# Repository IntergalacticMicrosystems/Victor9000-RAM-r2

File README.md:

# Victor9000-RAM-r2

WORK IN PROGRESS ~ DO NOT USE YET

The Victor9000-RAM-r2 is an attempt to modernize the design for cheaper manufacturing.

Jumper JP1 open is for use on a 256k motherboard, and JP1 closed is for a 128k motherboard.

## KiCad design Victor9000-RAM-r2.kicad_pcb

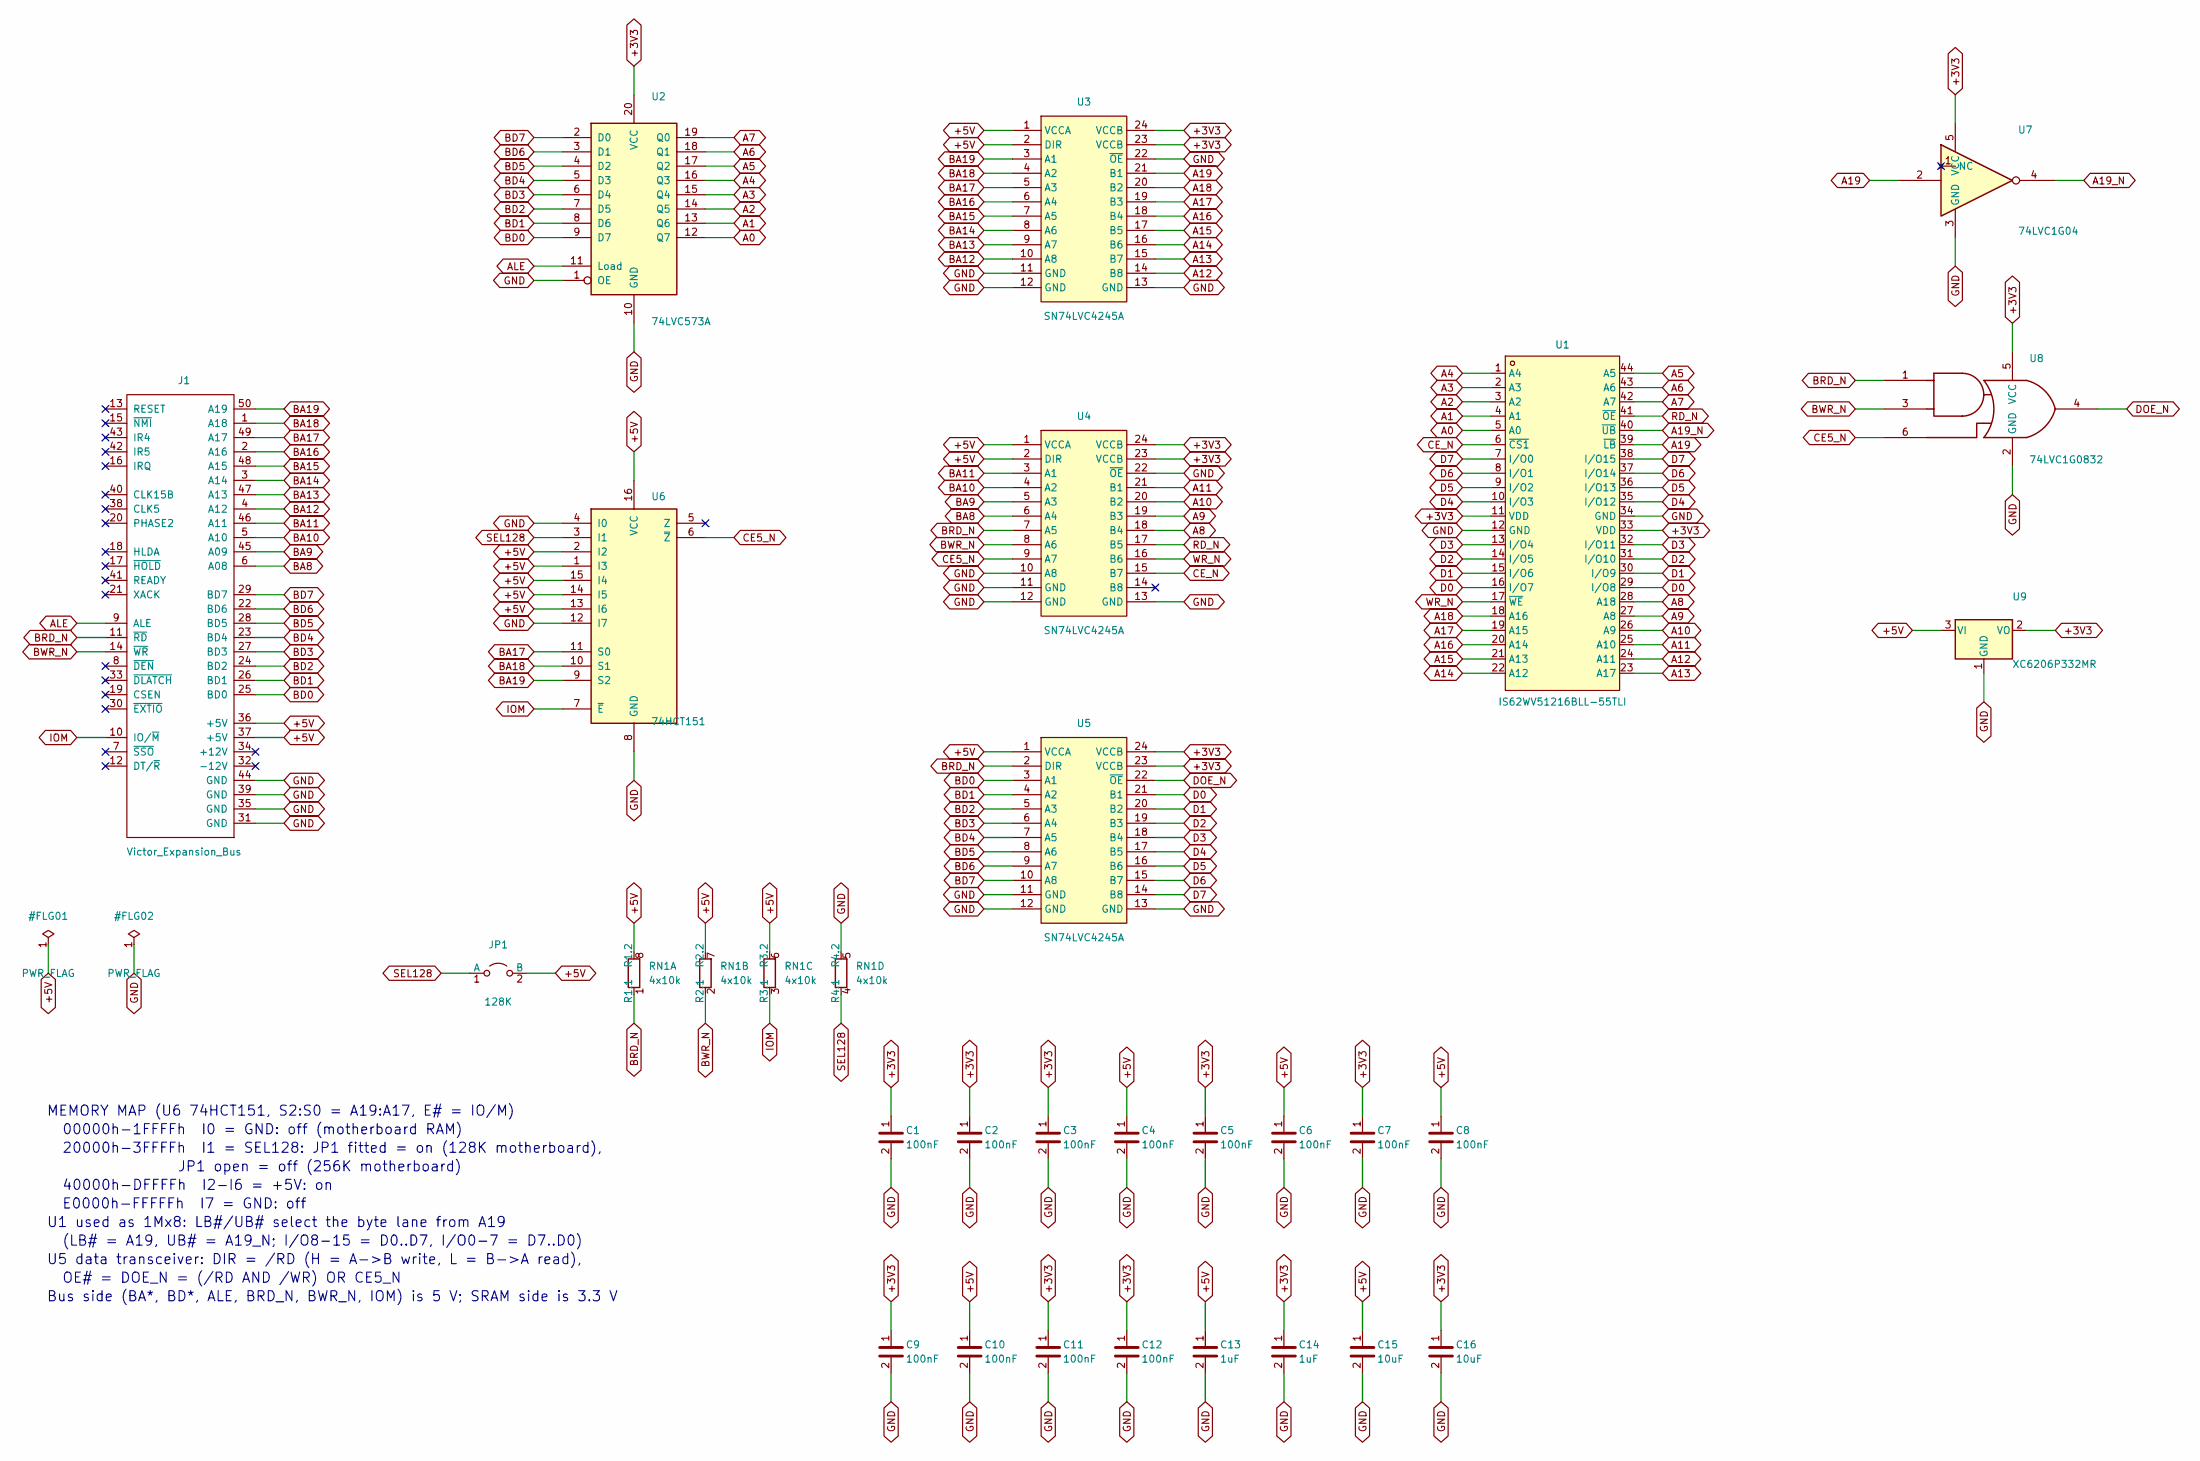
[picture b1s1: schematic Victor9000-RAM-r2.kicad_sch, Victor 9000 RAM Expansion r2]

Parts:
C1, C2, C3, C4, C5, C6, C7, C8, C9, C10, C11, C12: 100nF; C_0603_1608Metric; MPN CC0603KRX7R9BB104; LCSC C14663
C13, C14: 1uF; C_0603_1608Metric; MPN CL10A105KB8NNNC; LCSC C15849
C15, C16: 10uF; C_0805_2012Metric; MPN CL21A106KAYNNNE; LCSC C15850
J1: Victor_Expansion_Bus; Victor Expansion Edge Connector; MPN card-edge fingers
JP1: 128K; PinHeader_1x02_P2.54mm_Horizontal; MPN PZ254R-11-02P; LCSC C492410
RN1: 4x10k; R_Array_Convex_4x0603; MPN 4D03WGJ0103T5E; LCSC C29718
U1: IS62WV51216BLL-55TLI; TSOP-II-44_10.16x18.41mm_P0.8mm; MPN IS62WV51216BLL-55TLI; LCSC C11315
U2: 74LVC573A; TSSOP-20_4.4x6.5mm_P0.65mm; MPN 74LVC573APW,118; LCSC C6096
U3, U4, U5: SN74LVC4245A; TSSOP-24_4.4x7.8mm_P0.65mm; MPN SN74LVC4245APWR; LCSC C7859
U6: 74HCT151; SOIC-16_3.9x9.9mm_P1.27mm; MPN 74HCT151D,653; LCSC C547364
U7: 74LVC1G04; SOT-23-5; MPN SN74LVC1G04DBVR; LCSC C19829658
U8: 74LVC1G0832; SOT-23-6; MPN SN74LVC1G0832DBVR; LCSC C206101
U9: XC6206P332MR; SOT-23; MPN XC6206P332MR-G; LCSC C5446

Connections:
+3V3: C1.1, C2.1, C3.1, C5.1, C7.1, C9.1, C11.1, C12.1, C14.1, C16.1, U1.11 (VDD), U1.33 (VDD), U2.20 (VCC), U3.23 (VCCB), U3.24 (VCCB), U4.23 (VCCB), U4.24 (VCCB), U5.23 (VCCB), U5.24 (VCCB), U7.5 (VCC), U8.5 (VCC), U9.2 (VO)
+5V: C4.1, C6.1, C8.1, C10.1, C13.1, C15.1, J1.36 (+5V), J1.37 (+5V), JP1.2 (B), RN1.6 (R3.2), RN1.7 (R2.2), RN1.8 (R1.2), U3.1 (VCCA), U3.2 (DIR), U4.1 (VCCA), U4.2 (DIR), U5.1 (VCCA), U6.1 (I3), U6.2 (I2), U6.13 (I6), U6.14 (I5), U6.15 (I4), U6.16 (VCC), U9.3 (VI)
A0: U1.5 (A0), U2.12 (Q7)
A1: U1.4 (A1), U2.13 (Q6)
A2: U1.3 (A2), U2.14 (Q5)
A3: U1.2 (A3), U2.15 (Q4)
A4: U1.1 (A4), U2.16 (Q3)
A5: U1.44 (A5), U2.17 (Q2)
A6: U1.43 (A6), U2.18 (Q1)
A7: U1.42 (A7), U2.19 (Q0)
A8: U1.28 (A18), U4.18 (B4)
A9: U1.27 (A8), U4.19 (B3)
A10: U1.26 (A9), U4.20 (B2)
A11: U1.25 (A10), U4.21 (B1)
A12: U1.24 (A11), U3.14 (B8)
A13: U1.23 (A17), U3.15 (B7)
A14: U1.22 (A12), U3.16 (B6)
A15: U1.21 (A13), U3.17 (B5)
A16: U1.20 (A14), U3.18 (B4)
A17: U1.19 (A15), U3.19 (B3)
A18: U1.18 (A16), U3.20 (B2)
A19: U1.39 (~LB), U3.21 (B1), U7.2
A19_N: U1.40 (~UB), U7.4
ALE: J1.9 (ALE), U2.11 (Load)
BA8: J1.6 (A08), U4.6 (A4)
BA9: J1.45 (A09), U4.5 (A3)
BA10: J1.5 (A10), U4.4 (A2)
BA11: J1.46 (A11), U4.3 (A1)
BA12: J1.4 (A12), U3.10 (A8)
BA13: J1.47 (A13), U3.9 (A7)
BA14: J1.3 (A14), U3.8 (A6)
BA15: J1.48 (A15), U3.7 (A5)
BA16: J1.2 (A16), U3.6 (A4)
BA17: J1.49 (A17), U3.5 (A3), U6.11 (S0)
BA18: J1.1 (A18), U3.4 (A2), U6.10 (S1)
BA19: J1.50 (A19), U3.3 (A1), U6.9 (S2)
BD0: J1.25 (BD0), U2.9 (D7), U5.3 (A1)
BD1: J1.26 (BD1), U2.8 (D6), U5.4 (A2)
BD2: J1.24 (BD2), U2.7 (D5), U5.5 (A3)
BD3: J1.27 (BD3), U2.6 (D4), U5.6 (A4)
BD4: J1.23 (BD4), U2.5 (D3), U5.7 (A5)
BD5: J1.28 (BD5), U2.4 (D2), U5.8 (A6)
BD6: J1.22 (BD6), U2.3 (D1), U5.9 (A7)
BD7: J1.29 (BD7), U2.2 (D0), U5.10 (A8)
BRD_N: J1.11 (~RD), RN1.1 (R1.1), U4.7 (A5), U5.2 (DIR), U8.1
BWR_N: J1.14 (~WR), RN1.2 (R2.1), U4.8 (A6), U8.3
CE5_N: U4.9 (A7), U6.6 (~Z), U8.6
CE_N: U1.6 (~CS1), U4.15 (B7)
D0: U1.16 (I/O7), U1.29 (I/O8), U5.21 (B1)
D1: U1.15 (I/O6), U1.30 (I/O9), U5.20 (B2)
D2: U1.14 (I/O5), U1.31 (I/O10), U5.19 (B3)
D3: U1.13 (I/O4), U1.32 (I/O11), U5.18 (B4)
D4: U1.10 (I/O3), U1.35 (I/O12), U5.17 (B5)
D5: U1.9 (I/O2), U1.36 (I/O13), U5.16 (B6)
D6: U1.8 (I/O1), U1.37 (I/O14), U5.15 (B7)
D7: U1.7 (I/O0), U1.38 (I/O15), U5.14 (B8)
DOE_N: U5.22 (~OE), U8.4
GND: C1.2, C2.2, C3.2, C4.2, C5.2, C6.2, C7.2, C8.2, C9.2, C10.2, C11.2, C12.2, C13.2, C14.2, C15.2, C16.2, J1.31 (GND), J1.35 (GND), J1.39 (GND), J1.44 (GND), RN1.5 (R4.2), U1.12 (GND), U1.34 (GND), U2.1 (OE), U2.10 (GND), U3.11 (GND), U3.12 (GND), U3.13 (GND), U3.22 (~OE), U4.10 (A8), U4.11 (GND), U4.12 (GND), U4.13 (GND), U4.22 (~OE), U5.11 (GND), U5.12 (GND), U5.13 (GND), U6.4 (I0), U6.8 (GND), U6.12 (I7), U7.3 (GND), U8.2 (GND), U9.1 (GND)
IOM: J1.10 (IO/~M), RN1.3 (R3.1), U6.7 (~E)
RD_N: U1.41 (~OE), U4.17 (B5)
SEL128: JP1.1 (A), RN1.4 (R4.1), U6.3 (I1)
WR_N: U1.17 (~WE), U4.16 (B6)

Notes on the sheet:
MEMORY MAP (U6 74HCT151, S2:S0 = A19:A17, E# = IO/M)
00000h-1FFFFh I0 = GND: off (motherboard RAM)
20000h-3FFFFh I1 = SEL128: JP1 fitted = on (128K motherboard),
JP1 open = off (256K motherboard)
40000h-DFFFFh I2-I6 = +5V: on
E0000h-FFFFFh I7 = GND: off
U1 used as 1Mx8: LB#/UB# select the byte lane from A19
(LB# = A19, UB# = A19_N; I/O8-15 = D0..D7, I/O0-7 = D7..D0)
U5 data transceiver: DIR = /RD (H = A->B write, L = B->A read),
OE# = DOE_N = (/RD AND /WR) OR CE5_N
Bus side (BA*, BD*, ALE, BRD_N, BWR_N, IOM) is 5 V; SRAM side is 3.3 V

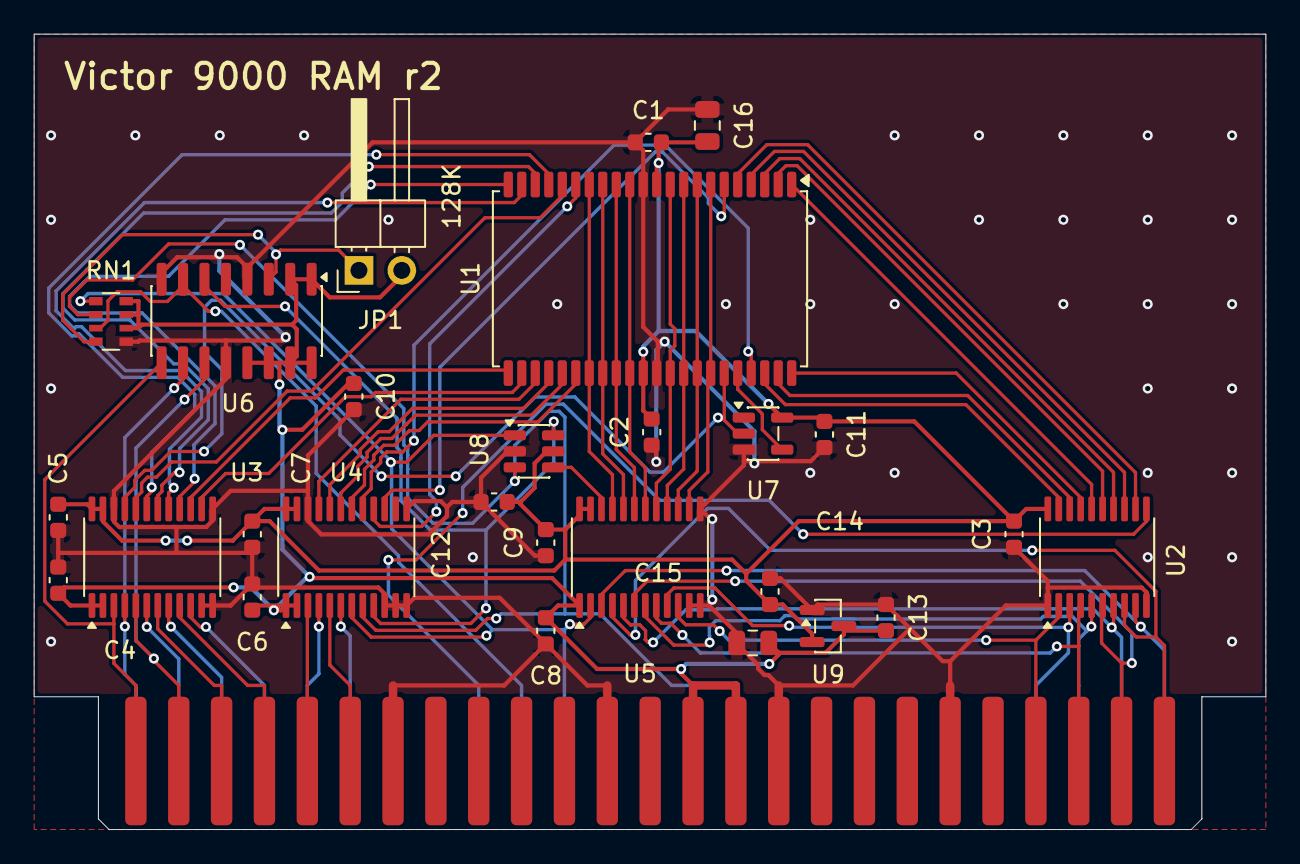
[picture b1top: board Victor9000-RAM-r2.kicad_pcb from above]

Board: 2 copper layers, 73.0 x 47.1 mm, 28 parts (0 on the bottom side), 62 nets.
